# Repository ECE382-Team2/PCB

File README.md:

# OreoFT PCB

We used the Capacitance Comb library to automatically generate various configurations of capacitive comb structures for our capacitive force-torque (FT) sensor. Using the library in double-sided mode allowed us to create identical electrode traces for the top and bottom layers, ensuring symmetry and consistency. This automated generation process streamlined our sensor bring-up and improved design repeatability across different PCB configurations.

## PCB Configurations
There are multiple PCB configurations that vary by trace width, trace spacing, and the overall diameter of the electrode array (the circle formed by the four quadrants of electrodes).

### Electrode Array Diameter: 35 mm

| Option | Trace Width (mm) | Trace Spacing (mm) |
|:-------:|:----------------:|:------------------:|
| 1 | 0.2 | 0.2 |
| 2 | 0.4 | 0.4 |
| 3 | 0.4 | 0.2 |

### Electrode Array Diameter: 52 mm

| Option | Trace Width (mm) | Trace Spacing (mm) |
|:-------:|:----------------:|:------------------:|
| 1 | 0.7 | 0.2 |
| 2 | 1.0 | 0.2 |
| 3 | 0.7 | 0.1 |

These configurations allow us to test how trace geometry and sensor diameter affect the sensor's response and sensitivity. 
Different trace configurations can be generated using the Capacitance Comb library parameters accordingly.

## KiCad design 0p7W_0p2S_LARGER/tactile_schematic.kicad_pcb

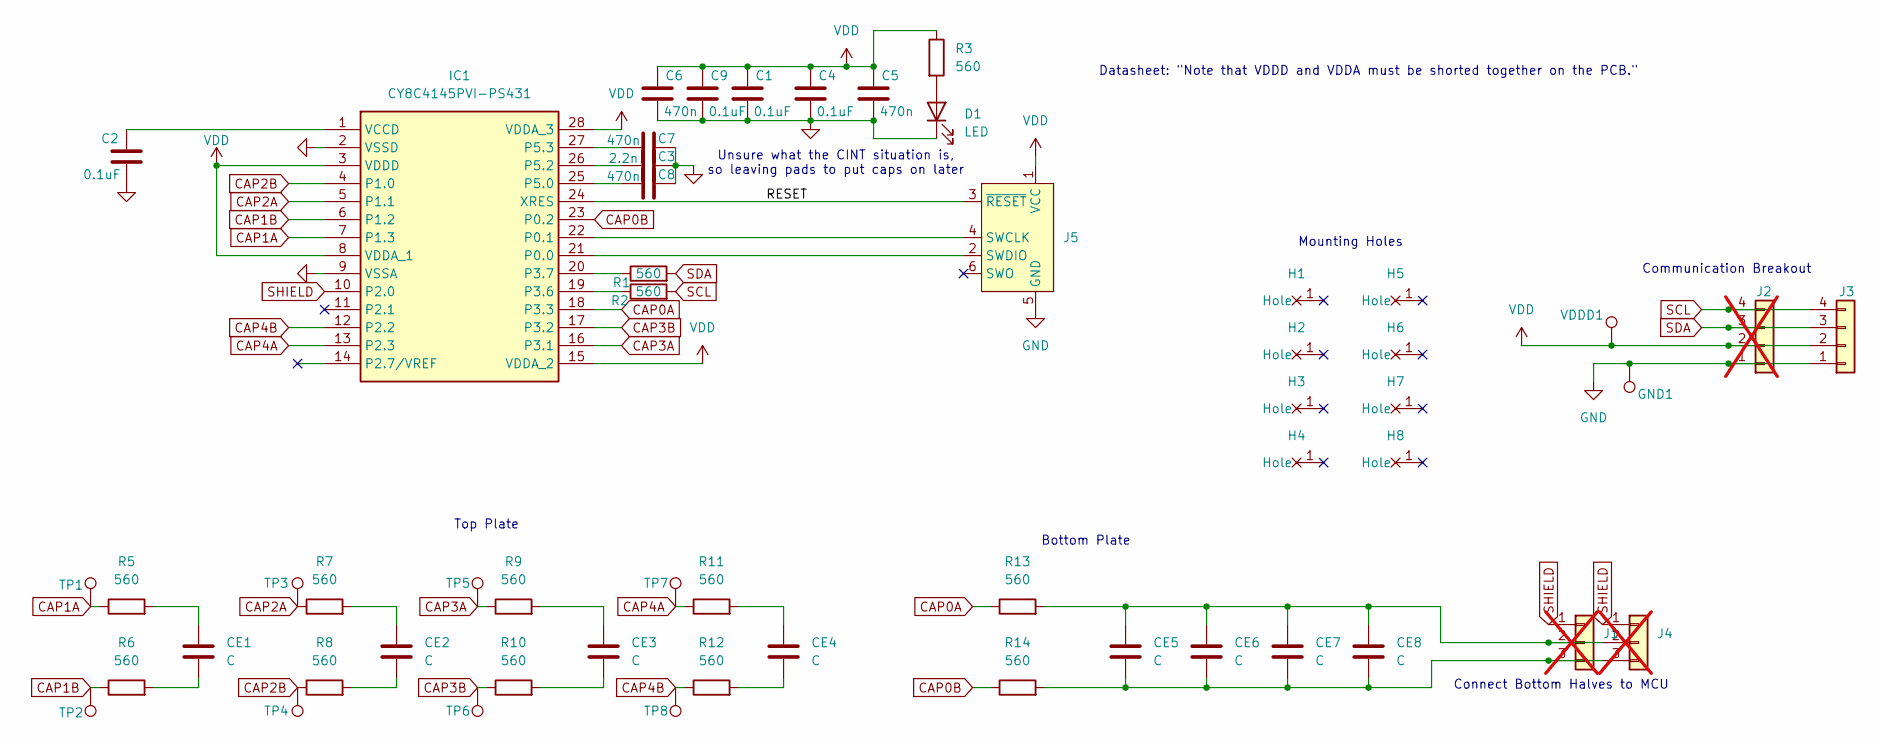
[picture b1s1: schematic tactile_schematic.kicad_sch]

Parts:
C1, C2, C4, C9: 0.1uF; C_0603_1608Metric_Pad1.08x0.95mm_HandSolder
C3: 2.2n; C_0603_1608Metric_Pad1.08x0.95mm_HandSolder
C5, C6, C7, C8: 470n; C_0603_1608Metric_Pad1.08x0.95mm_HandSolder
CE1, CE2, CE3, CE4: C; 07W_02S_52D_COIL_BACK
CE5, CE6, CE7, CE8: C; 07W_02S_52D_COIL_FRONT
D1: LED; LED_0603_1608Metric
GND1: TestPoint; TestPoint_THTPad_D1.0mm_Drill0.5mm
H1, H2, H3, H4, H5, H6, H7, H8: MountingHole_3.2mm_M3_Pad
IC1: CY8C4145PVI-PS431; SOP65P780X200-28N; Manufacturer_Part_Number CY8C4145PVI-PS431
J1, J4: Conn_01x03; PinHeader_1x03_P2.00mm_Vertical; not fitted
J2: Conn_01x04; PinHeader_1x04_P1.27mm_Vertical; not fitted
J3: Conn_01x04; JST_SH_SM04B-SRSS-TB_1x04-1MP_P1.00mm_Horizontal
J5: Conn_ARM_SWD_TagConnect_TC2030-NL; Tag-Connect_TC2030-IDC-NL_2x03_P1.27mm_Vertical
R1, R2, R3, R5, R6, R7, R8, R9, R10, R11, R12, R13, R14: 560; R_0603_1608Metric_Pad0.98x0.95mm_HandSolder
TP1, TP2, TP3, TP4, TP5, TP6, TP7, TP8: TestPoint; TestPoint_THTPad_D1.0mm_Drill0.5mm
VDDD1: TestPoint; TestPoint_THTPad_D1.0mm_Drill0.5mm

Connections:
/RESET: IC1.24 (XRES), J5.3 (~RESET)
CAP0A: IC1.18 (P3.3), R13.1
CAP0B: IC1.23 (P0.2), R14.1
CAP1A: IC1.7 (P1.3), R5.1, TP1.1
CAP1B: IC1.6 (P1.2), R6.1, TP2.1
CAP2A: IC1.5 (P1.1), R7.1, TP3.1
CAP2B: IC1.4 (P1.0), R8.1, TP4.1
CAP3A: IC1.16 (P3.1), R9.1, TP5.1
CAP3B: IC1.17 (P3.2), R10.1, TP6.1
CAP4A: IC1.13 (P2.3), R11.1, TP7.1
CAP4B: IC1.12 (P2.2), R12.1, TP8.1
GND: C1.2, C2.2, C3.2, C4.2, C5.2, C6.2, C7.2, C8.2, C9.2, D1.1 (K), GND1.1, IC1.2 (VSSD), IC1.9 (VSSA), J2.1, J3.1, J5.5 (GND)
unnamed: CE1.1, R5.2
unnamed: CE1.2, R6.2
unnamed: CE2.1, R7.2
unnamed: CE2.2, R8.2
unnamed: CE3.1, R9.2
unnamed: CE3.2, R10.2
unnamed: CE4.1, R11.2
unnamed: CE4.2, R12.2
unnamed: D1.2 (A), R3.2
unnamed: IC1.21 (P0.0), J5.2 (SWDIO)
unnamed: IC1.22 (P0.1), J5.4 (SWCLK)
unnamed: IC1.19 (P3.6), R2.1
unnamed: IC1.20 (P3.7), R1.1
unnamed: C8.1, IC1.25 (P5.0)
unnamed: C3.1, IC1.26 (P5.2)
unnamed: C7.1, IC1.27 (P5.3)
unnamed: C2.1, IC1.1 (VCCD)
unnamed: CE5.1, CE6.1, CE7.1, CE8.1, J1.2, J4.2, R13.2
unnamed: CE5.2, CE6.2, CE7.2, CE8.2, J1.3, J4.3, R14.2
SCL: J2.4, J3.4, R2.2
SDA: J2.3, J3.3, R1.2
SHIELD: IC1.10 (P2.0), IC1.14 (P2.7/VREF), J1.1, J4.1
VDD: C1.1, C4.1, C5.1, C6.1, C9.1, IC1.3 (VDDD), IC1.8 (VDDA_1), IC1.15 (VDDA_2), IC1.28 (VDDA_3), J2.2, J3.2, J5.1 (VCC), R3.1, VDDD1.1

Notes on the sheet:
Datasheet: "Note that VDDD and VDDA must be shorted together on the PCB."
Top Plate
Mounting Holes
Unsure what the CINT situation is, so leaving pads to put caps on later
Bottom Plate
Communication Breakout
Connect Bottom Halves to MCU

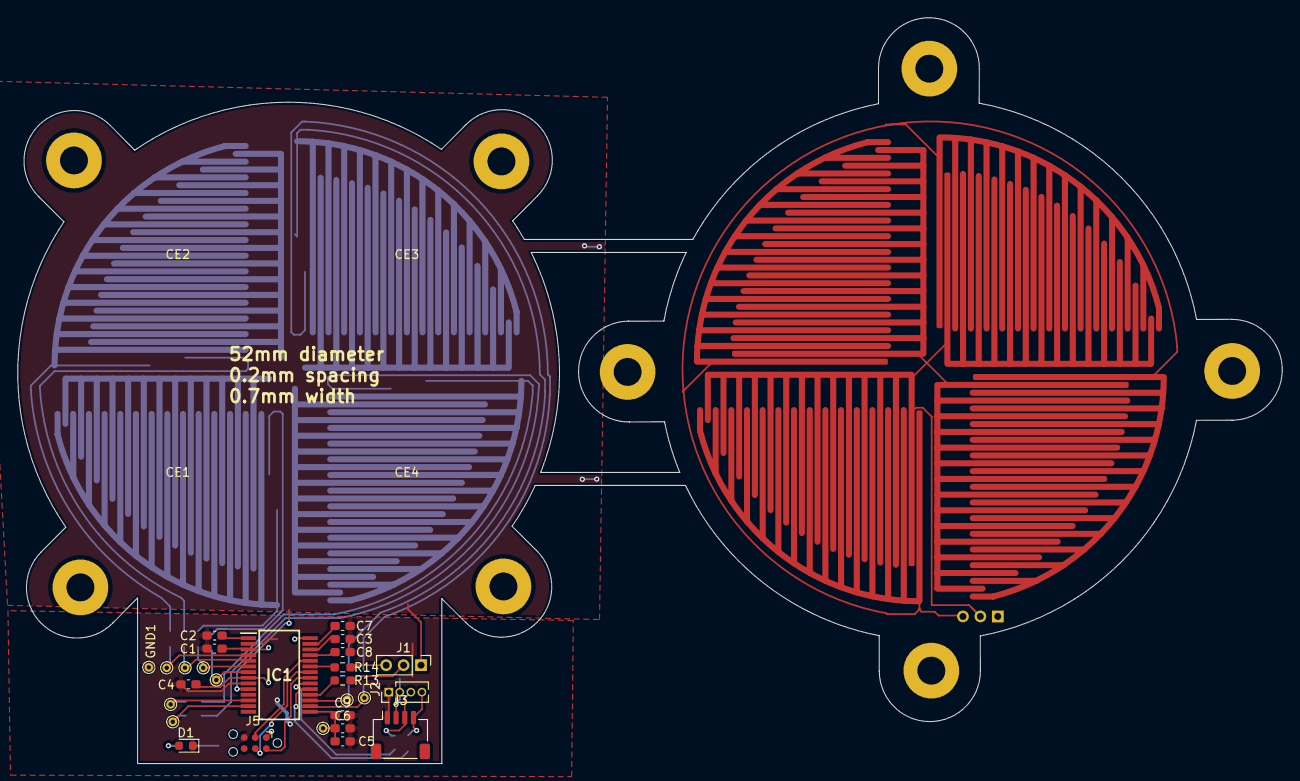
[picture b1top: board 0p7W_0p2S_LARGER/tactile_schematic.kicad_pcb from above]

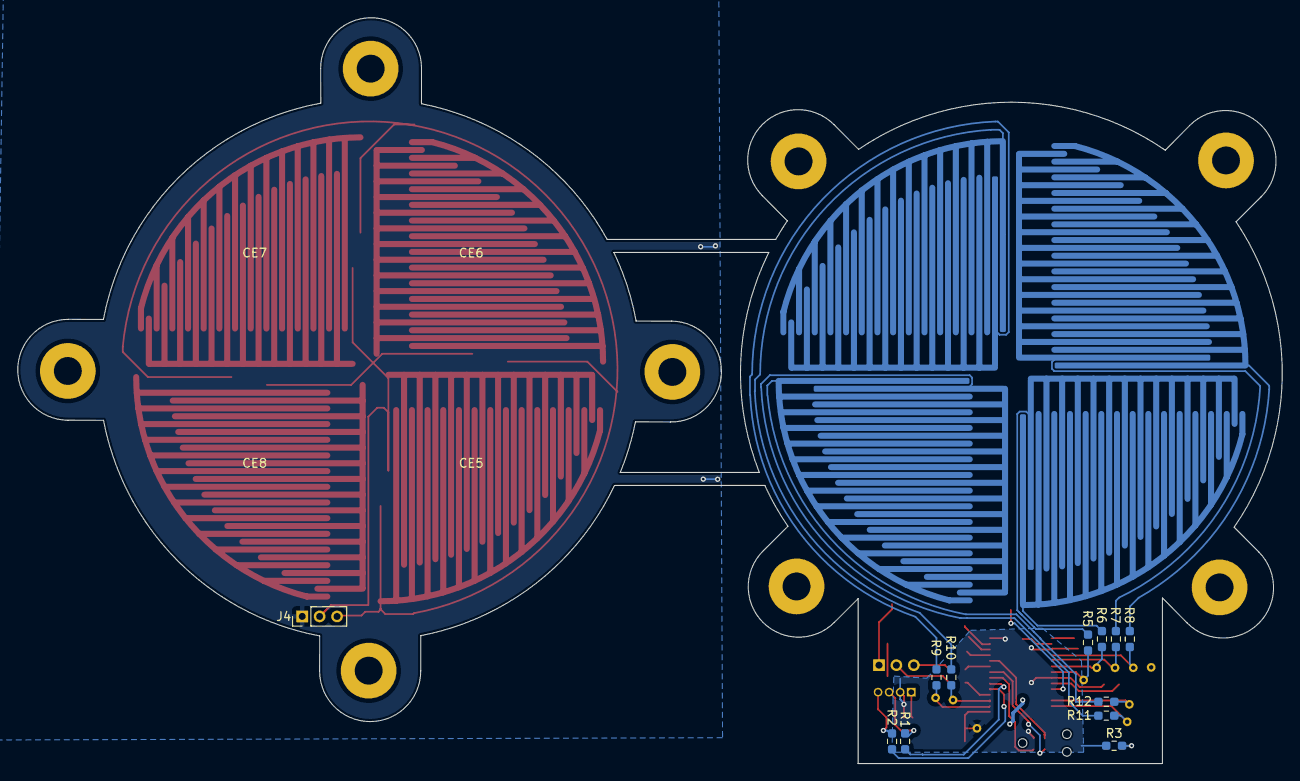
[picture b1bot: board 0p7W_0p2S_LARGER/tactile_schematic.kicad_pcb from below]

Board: 2 copper layers, 145.2 x 85.6 mm, 55 parts (12 on the bottom side), 35 nets.

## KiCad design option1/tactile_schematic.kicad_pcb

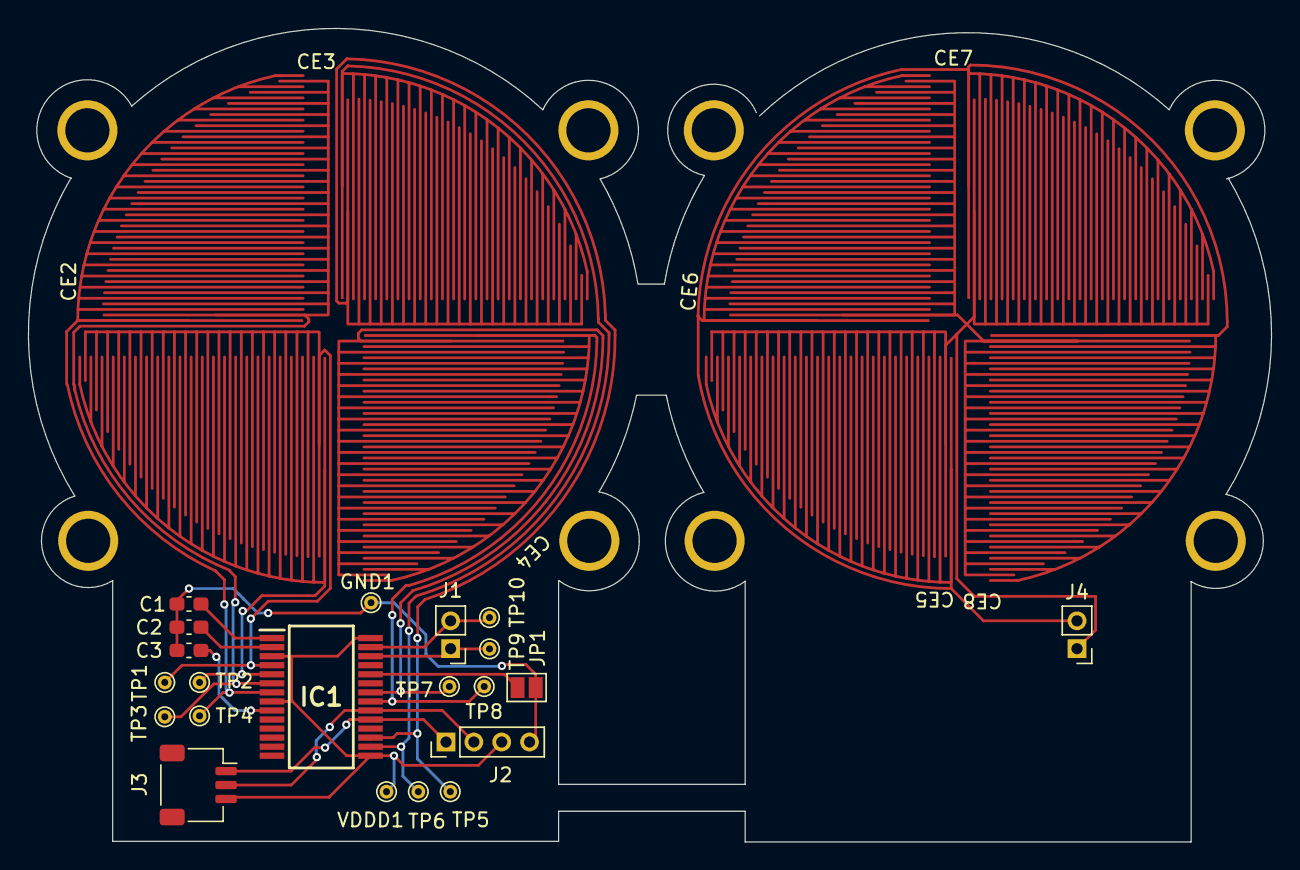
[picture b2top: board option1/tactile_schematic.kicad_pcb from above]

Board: 2 copper layers, 89.3 x 58.4 mm, 37 parts (0 on the bottom side), 18 nets.

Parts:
C1, C2, C3: 0.1uF; C_0603_1608Metric_Pad1.08x0.95mm_HandSolder
CE1, CE2, CE3, CE4, CE5, CE6, CE7, CE8: C; COIL_GENERATOR
GND1: TestPoint; TestPoint_THTPad_D1.0mm_Drill0.5mm
H1, H2, H3, H4, H5, H6, H7, H8: MountingHole_4_40
IC1: CY8C4145PVI-PS431; SOP65P780X200-28N
J1, J4: Conn_01x02; PinHeader_1x02_P2.00mm_Vertical
J2: Conn_01x04; PinHeader_1x04_P2.00mm_Vertical
J3: Conn_01x04; JST_SH_SM03B-SRSS-TB_1x03-1MP_P1.00mm_Horizontal
JP1: SolderJumper_2_Open; SolderJumper-2_P1.3mm_Open_Pad1.0x1.5mm
TP1, TP2, TP3, TP4, TP5, TP6, TP7, TP8, TP9, TP10: TestPoint; TestPoint_THTPad_D1.0mm_Drill0.5mm
VDDD1: TestPoint; TestPoint_THTPad_D1.0mm_Drill0.5mm

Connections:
GND: C1.2, C2.2, C3.2, GND1.1, J2.4, JP1.2 (B)
unnamed: C1.1, IC1.1 (VCCD)
unnamed: C3.1, IC1.9 (VSSA)
unnamed: C2.1, IC1.2 (VSSD)
unnamed: IC1.24 (XRES), JP1.1 (A)
P0.0: CE4.2, IC1.21 (P0.0), TP8.1
P0.1: CE4.1, IC1.22 (P0.1), TP7.1
P1.0: CE1.1, IC1.4 (P1.0), TP1.1
P1.1: CE1.2, IC1.5 (P1.1), TP2.1
P1.2: CE2.1, IC1.6 (P1.2), TP3.1
P1.3: CE2.2, IC1.7 (P1.3), TP4.1
P3.1: CE3.2, IC1.16 (P3.1), TP6.1
P3.2: CE3.1, IC1.17 (P3.2), TP5.1
P3.6: IC1.19 (P3.6), J2.1, J3.1
P3.7: IC1.20 (P3.7), J2.2, J3.2
P5.2: CE5.1, CE6.1, CE7.1, CE8.1, IC1.26 (P5.2), J1.1, J4.1, TP9.1
P5.3: CE5.2, CE6.2, CE7.2, CE8.2, IC1.27 (P5.3), J1.2, J4.2, TP10.1
VDDA_1: IC1.3 (VDDD), IC1.8 (VDDA_1), IC1.15 (VDDA_2), IC1.28 (VDDA_3), J2.3, J3.3, VDDD1.1

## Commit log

2025-09-09 started coinft schematic, uploaded A7417AR model
2025-09-22 initial schematic and layout upload
2025-09-23 need to fix edge cuts not lining up
2025-09-24 PCB first draft
2025-09-24 redid layout, pushed circuits down a bit
2025-09-24 fixed silkscreen
2025-09-25 schematic file
2025-09-29 many changes
2025-09-29 KiCAD mod files
2025-09-30 three pcb trace configurations
2025-10-25 - remove RST pad - change all resistors to 560ohm - remove UART test points - relayout with cleaning - conosolidate down to 3 capacitor values (replace 1uf w/ paralel 2 470ufs) - add power LED - move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
2025-10-27 three new pbs initial upload
2025-10-27 first and second pcb iteration configurations
2025-10-27 gitignore *.lck
2025-10-28 update configs
2025-10-28 0.7mm width, 0.1 spacing, 52mm diameter initial upload
2025-10-28 rm old configs
2025-10-28 update pcb configs
2025-10-29 make spacing fixes (first two boards)
2025-10-29 more spacing fixes
2025-10-29 last sizing + pin2.7 changes
2025-10-29 trace thickness & rebuild planes
2025-10-29 move prog connector up, make bottom of gnd plane connected propelrly
2025-10-29 straightened gnd plane
2025-10-29 fix gnd plane
2025-10-29 wills trace changes
2025-10-29 remove redundant gnd trace by scl on larger pcbs
2025-10-29 fixed drc error
2025-10-29 Last trace changes by will
2025-11-03 rm unused files
2025-12-10 renamed
